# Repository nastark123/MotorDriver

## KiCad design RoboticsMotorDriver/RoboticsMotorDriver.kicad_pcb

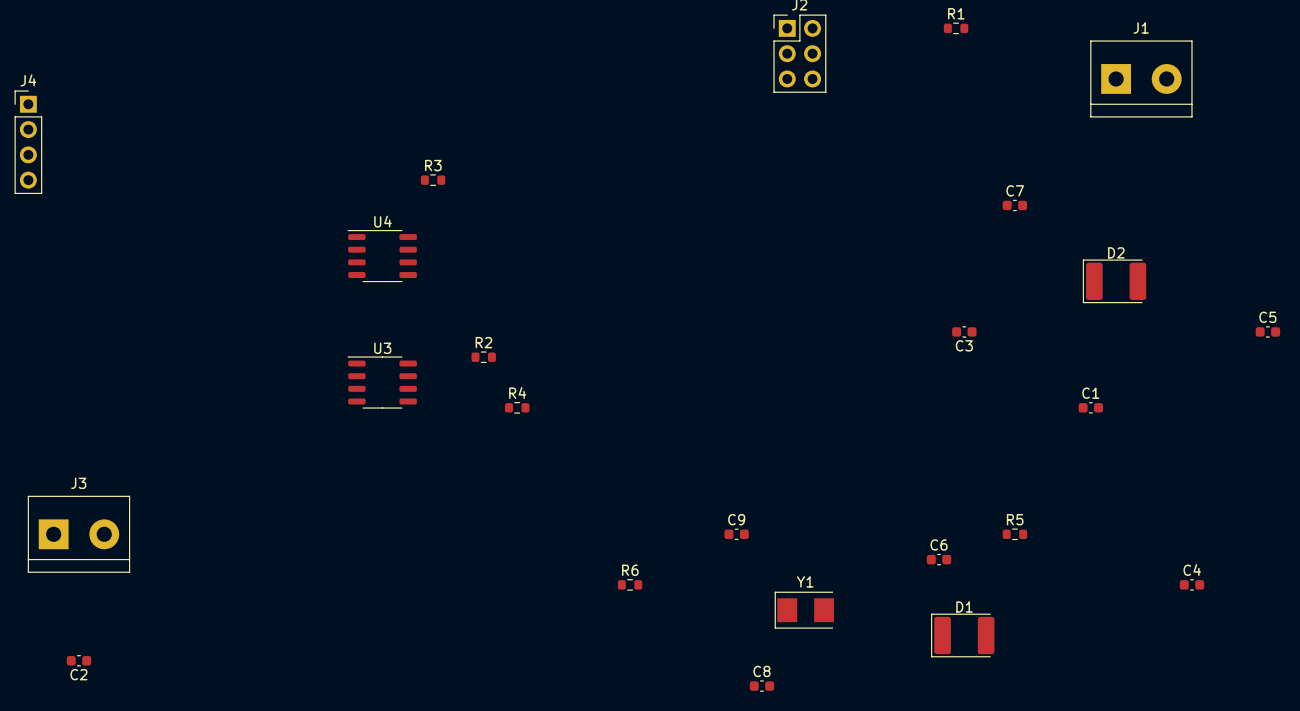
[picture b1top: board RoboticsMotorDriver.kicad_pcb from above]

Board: 2 copper layers, 24 parts (0 on the bottom side), 16 nets, no tracks yet.

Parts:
C1, C4, C5: 100nF; C_0603_1608Metric
C2, C3: 10uF; C_0603_1608Metric
C6, C7: 1uF; C_0603_1608Metric
C8, C9: 16pF; C_0603_1608Metric
D1, D2: D_Schottky; D_2114_3652Metric
J1, J3: Screw_Terminal_01x02; TerminalBlock_bornier-2_P5.08mm
J2: Conn_02x03_Counter_Clockwise; PinHeader_2x03_P2.54mm_Vertical
J4: Conn_01x04; PinHeader_1x04_P2.54mm_Vertical
R1: 10K; R_0603_1608Metric
R2, R3, R4, R5: 100; R_0603_1608Metric
R6: 1 M; R_0603_1608Metric
U3, U4: HALF_BRIDGE_DRIVER_DGD2003; SO-8_3.9x4.9mm_P1.27mm
Y1: 16 MHz; Crystal_SMD_5032-2Pin_5.0x3.2mm

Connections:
+5V: C1.2, C3.1, J2.6, J4.3, R1.2
+12V: C2.1, J3.2
/DRIVER_HIGH_0: R2.1, U3.7 (HO)
/DRIVER_HIGH_1: R3.2, U4.7 (HO)
/DRIVER_LOW_0: R4.1, U3.5 (LO)
/DRIVER_LOW_1: R5.2, U4.5 (LO)
GND: C1.1, C2.2, C3.2, C4.1, C5.1, C8.2, C9.2, J2.4, J3.1, J4.4, U3.4 (COM), U4.4 (COM)
unnamed: C4.2, D1.2 (A), U3.1 (VCC)
unnamed: C5.2, D2.2 (A), U4.1 (VCC)
unnamed: C6.1, D1.1 (K), U3.8 (VB)
unnamed: C6.2, U3.6 (VS)
unnamed: C7.1, D2.1 (K), U4.8 (VB)
unnamed: C7.2, U4.6 (VS)
unnamed: C8.1, R6.1, Y1.2
unnamed: C9.1, R6.2, Y1.1
unnamed: J2.1, R1.1

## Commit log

2022-06-25 Project updates
2022-06-25 Added KiCad project
2022-06-29 Updated KiCAD schematic
2022-07-04 Added more components and fixed issues in schematic
2022-07-17 Design updates
